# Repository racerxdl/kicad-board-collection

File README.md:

# Kicad Board Collection

Kicad Board Collection for use in 3D Projects

Sometimes I re-create the PCBs that I buy from Aliexpress and other sellers in Kicad so I can use the Freecad KicadStepUp plugin to generate a STEP file so I can use for drawing my 3D Printed models. Since
I thought it might be usefull for some other people, I decided to just collect them inside a github repository.

## Current Collection

* [AS5600 12-bit Absolute Encoder](AS5600/README.md)
* [CJMCU MPU-925x IMU](CJMCU-925x/README.md)
* [MPU6050 IMU](MPU6050/README.md)

## Warnings and Limitations

These are done to have an _almost_ perfect match with the boards I got. But the goal is to have a close enough board so I can use in my 3D Assemblies inside Freecad. Feel free to make a pull request to improve the accuracy with the real board.

You're free to use to anything you want (even producing those boards here and selling it) just keep in mind that:

* I haven't tested any of those designs
* They're made for generating STEP files and not GERBER files
* You will not blame me or anyone that contributed to this repository if something doesn't work as expected

## Contributing

Feel free to fork and add boards to this project and then make a pull request. I just expect that:

1. Board is made in Kicad
2. It has the PCB traces (basically it should represent a working board)
3. Should have a README.md inside the board folder with a picture of the 3D Model
4. The board size, holes and component positions should match the real board. The PCB traces doesnt need to match (you can route by yourself differently than the real board since it does not affect the 3D Model)
5. Preferably with the generated STEP file using Freecad
6. If you did the kicad drawing and the STEP file, an affiliate link for where to buy the board is allowed in the README as a reference where to buy.

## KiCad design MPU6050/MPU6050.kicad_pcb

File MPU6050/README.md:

# MPU6050 IMU

[STEP File](MPU6050.step)

# Where to buy

[https://s.click.aliexpress.com/e/_Abl2sP](https://s.click.aliexpress.com/e/_Abl2sP)

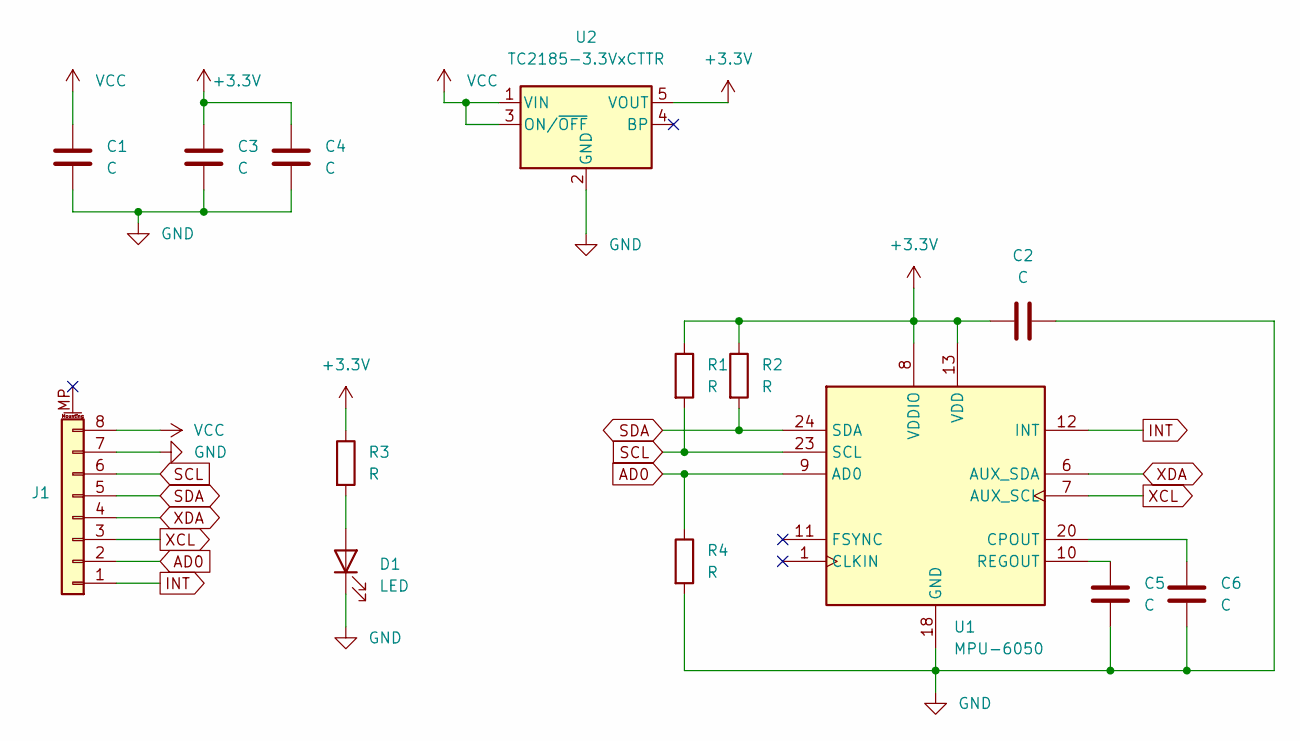
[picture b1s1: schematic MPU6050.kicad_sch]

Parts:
C1, C2, C3, C4, C5, C6: C; C_0603_1608Metric
D1: LED; LED_0603_1608Metric
J1: Conn_01x08_MountingPin; PinHeader_1x08_P2.54mm_Vertical
R1, R2, R3, R4: R; R_0603_1608Metric
U1: MPU-6050; InvenSense_QFN-24_4x4mm_P0.5mm
U2: TC2185-3.3VxCTTR; SOT-23-5

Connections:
+3V3: C2.1, C3.1, C4.1, R1.1, R2.1, R3.1, U1.8 (VDDIO), U1.13 (VDD), U2.5 (VOUT)
AD0: J1.2, R4.1, U1.9 (AD0)
GND: C1.2, C2.2, C3.2, C4.2, C5.2, C6.2, D1.1 (K), J1.7, R4.2, U1.18 (GND), U2.2 (GND)
INT: J1.1, U1.12 (INT)
unnamed: D1.2 (A), R3.2
unnamed: C5.1, U1.10 (REGOUT)
unnamed: C6.1, U1.20 (CPOUT)
SCL: J1.6, R1.2, U1.23 (SCL)
SDA: J1.5, R2.2, U1.24 (SDA)
VCC: C1.1, J1.8, U2.1 (VIN), U2.3 (ON/~OFF)
XCL: J1.3, U1.7 (AUX_SCL)
XDA: J1.4, U1.6 (AUX_SDA)

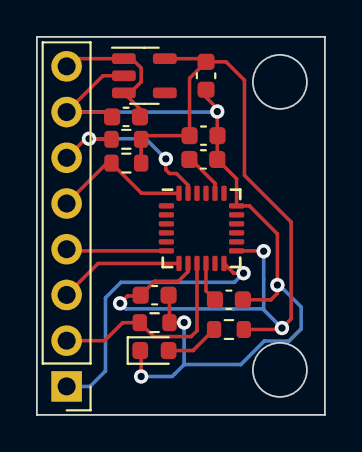
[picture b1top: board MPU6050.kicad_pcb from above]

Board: 2 copper layers, 16.0 x 21.0 mm, 14 parts (0 on the bottom side), 12 nets.

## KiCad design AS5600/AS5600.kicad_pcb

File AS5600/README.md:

# AS5600 12-bit Absolute Encoder

[STEP File](AS5600.step)

# Caveats

In the real board the 4 pin header is a bit more to the top of the board than in the current model, so at least a 1mm tolerance should be considered.

# Where to buy

[https://s.click.aliexpress.com/e/_APSxKB](https://s.click.aliexpress.com/e/_APSxKB)

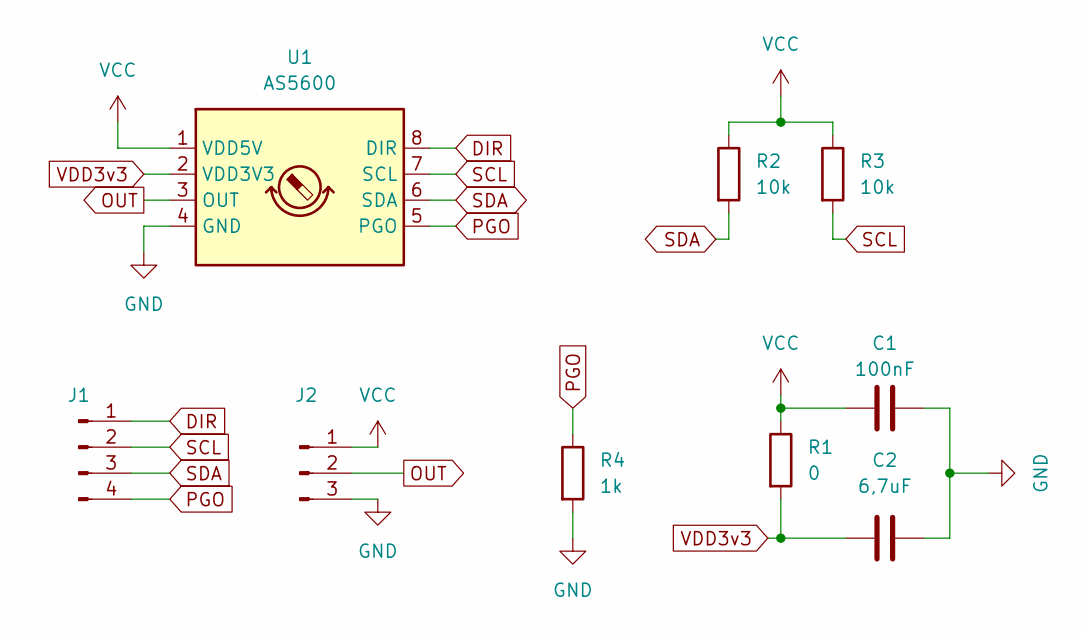
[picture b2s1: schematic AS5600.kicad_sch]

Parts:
C1: 100nF; C_0805_2012Metric_Pad1.18x1.45mm_HandSolder
C2: 6,7uF; C_0805_2012Metric_Pad1.18x1.45mm_HandSolder
J1: Conn_01x04_Male; PinHeader_1x04_P2.54mm_Vertical
J2: Conn_01x03_Male; PinHeader_1x03_P2.54mm_Vertical
R1: 0; R_0805_2012Metric_Pad1.20x1.40mm_HandSolder
R2, R3: 10k; R_0805_2012Metric_Pad1.20x1.40mm_HandSolder
R4: 1k; R_0805_2012Metric_Pad1.20x1.40mm_HandSolder
U1: AS5600; SOIC-8_3.9x4.9mm_P1.27mm

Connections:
DIR: J1.1, U1.8 (DIR)
GND: C1.2, C2.2, J2.3, R4.2, U1.4 (GND)
OUT: J2.2, U1.3 (OUT)
PGO: J1.4, R4.1, U1.5 (PGO)
SCL: J1.2, R3.2, U1.7 (SCL)
SDA: J1.3, R2.2, U1.6 (SDA)
VCC: C1.1, J2.1, R1.1, R2.1, R3.1, U1.1 (VDD5V)
VDD3v3: C2.1, R1.2, U1.2 (VDD3V3)

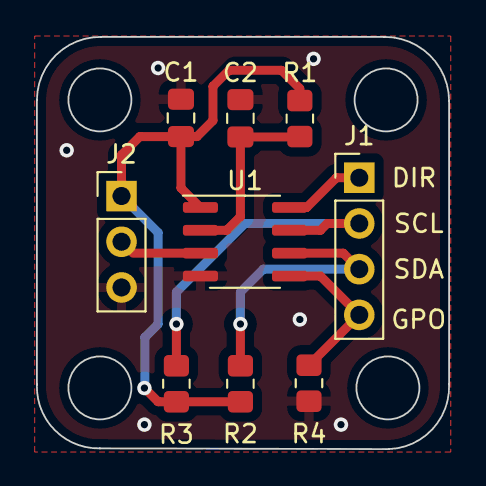
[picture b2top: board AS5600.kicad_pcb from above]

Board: 2 copper layers, 22.9 x 22.9 mm, 9 parts (0 on the bottom side), 8 nets.

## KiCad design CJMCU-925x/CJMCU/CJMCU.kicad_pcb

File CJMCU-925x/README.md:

# CJMCU MPU-925x IMU

[STEP File](CJMCU-925x.step)

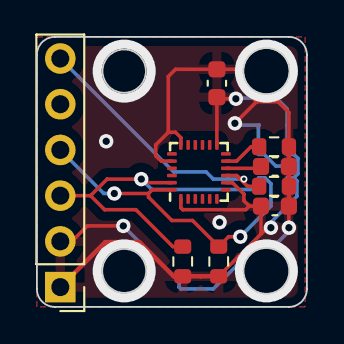
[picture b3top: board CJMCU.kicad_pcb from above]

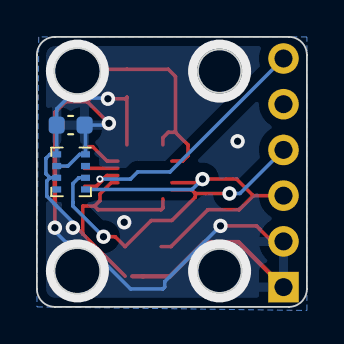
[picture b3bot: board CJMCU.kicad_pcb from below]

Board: 2 copper layers, 15.0 x 15.0 mm, 11 parts (2 on the bottom side), 6 nets.

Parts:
C1, C2, C3, C4: 100nF; C_0603_1608Metric
J1: Conn_01x06_Male; PinHeader_1x06_P2.54mm_Vertical
R1, R3: 1k; R_0603_1608Metric
R2, R4: 4k7; R_0603_1608Metric
U1: MPU-9250; InvenSense_QFN-24_3x3mm_P0.4mm
U2: BMP280; Bosch_LGA-8_2x2.5mm_P0.65mm_ClockwisePinNumbering

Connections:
AD0: J1.6, R1.1, U1.9 (AD0/MISO)
GND: C1.2, C2.1, C2.2, C3.1, C3.2, C4.1, C4.2, J1.1, J1.2, R1.2, R2.1, R3.1, R4.1, U1.1 (RESV_VDDIO), U1.8 (VDDIO), U1.13 (VDD), U1.18 (GND), U1.20 (RESV_GND), U2.1 (GND), U2.6 (VDDIO), U2.7 (GND), U2.8 (VDD)
unnamed: C1.1, U1.10 (REGOUT)
unnamed: R3.2, U1.11 (FSYNC)
SCL: J1.3, R4.2, U1.23 (SCL/SCLK), U2.4 (SCK)
SDA: J1.4, R2.2, U1.24 (SDA/MOSI), U2.3 (SDI)

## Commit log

2022-03-20 (preview)
2022-03-20 Add readme's
